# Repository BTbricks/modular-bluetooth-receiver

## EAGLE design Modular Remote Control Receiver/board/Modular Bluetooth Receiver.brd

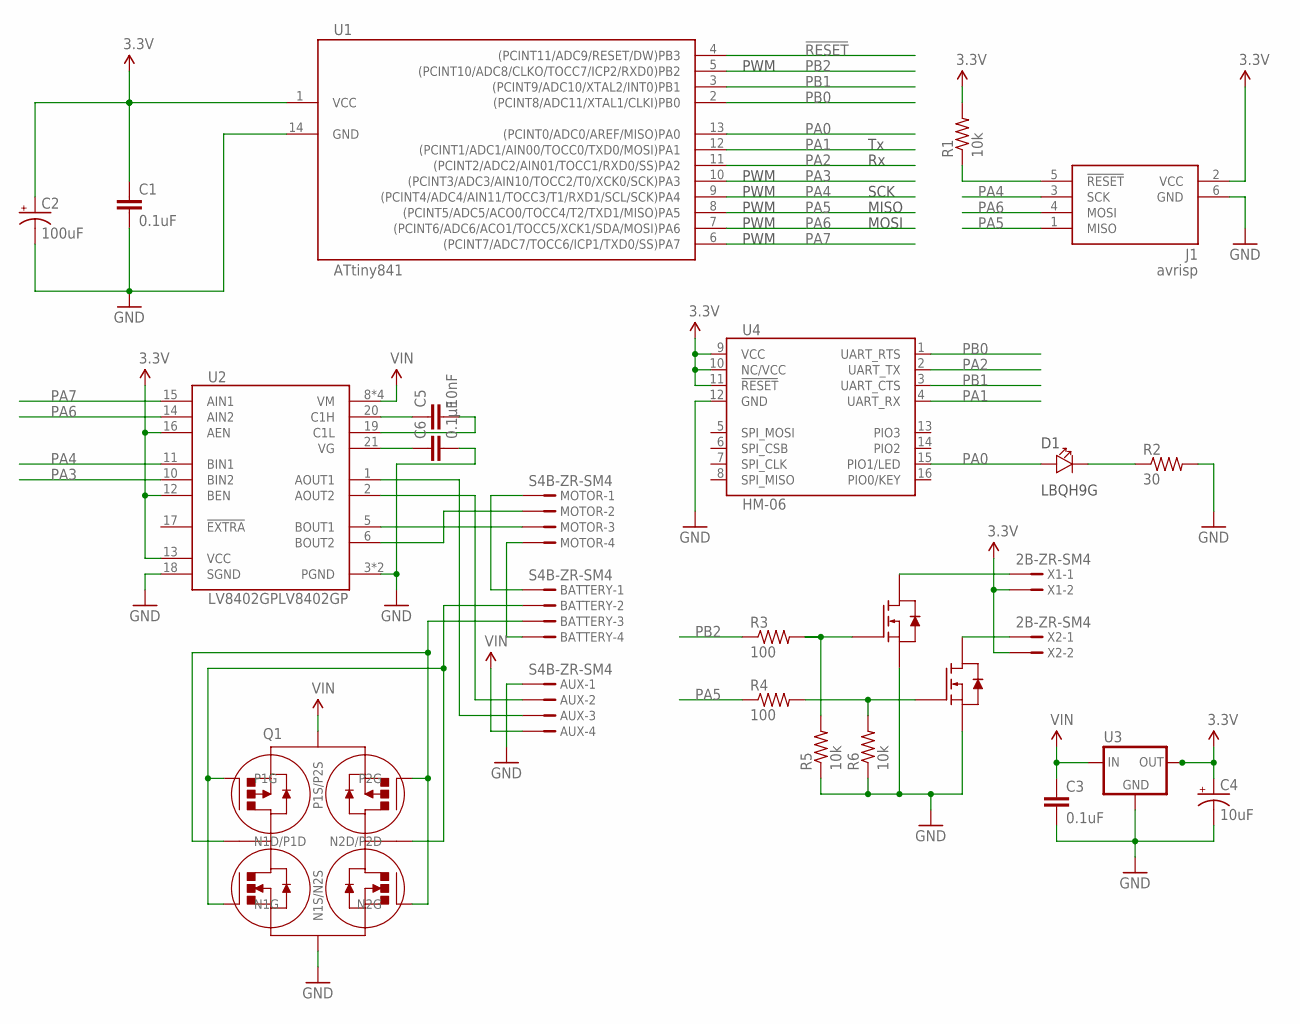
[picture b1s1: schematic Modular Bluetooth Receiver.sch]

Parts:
AUX: S4B-ZR-SM4
BATTERY: S4B-ZR-SM4
C1: 0.1uF; 0402; PARTNO 0603YC104KAT2A
C2: 100uF; 1206; PARTNO MCTT21X106M6R3CT
C3: 0.1uF; 0402
C4: 10uF; 1206
C5: 10nF; 0402
C6: 0.1µF; 0402
D1: LBQH9G; 0402_POL
J1: avrisp; CON6P2R
MOTOR: S4B-ZR-SM4
Q1: DMHC3025LSD-13; SO8
Q2: DMN32D2LV; SOT-563
R1, R5, R6: 10k; 0402; PARTNO ERJ-3GEYJ103V
R2: 30; 0402
R3, R4: 100; 0402
U1: ATtiny841; 14SOICN
U2: LV8402GPLV8402GP; VCT24
U3: RT9164A; SOT223
U4: HM-06; HM-05/06/07
X1, X2: 2B-ZR-SM4; S2B-ZR-SM4

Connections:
3.3V: C1.1, C2.1 (+), C4.1 (+), J1.2 (VCC), R1.2, U1.1 (VCC), U2.12 (BEN), U2.13 (VCC), U2.16 (AEN), U3.2 (OUT), U3.4 (OUT), U4.9 (VCC), U4.10 (NC/VCC), U4.11 (!RESET), X1.2, X2.2
!RESET: J1.5 (!RESET), R1.1, U1.4 ((PCINT11/ADC9/RESET/DW)PB3)
GND: AUX.1, C1.2, C2.2 (-), C3.2, C4.2 (-), C6.2, J1.6 (GND), Q1.P$3 (N1S/N2S), Q2.P$1 (SOURCE), Q2.P$4 (SOURCE), R2.2, R5.1, R6.1, U1.14 (GND), U2.3 (PGND), U2.4 (PGND), U2.18 (SGND), U3.1 (GND), U4.12 (GND)
unnamed: BATTERY.1, MOTOR.1
unnamed: BATTERY.4, MOTOR.4
unnamed: MOTOR.3, U2.5 (BOUT1)
unnamed: Q2.P$6 (DRAIN), X1.1
unnamed: AUX.3, U2.1 (AOUT1)
unnamed: AUX.2, U2.2 (AOUT2)
unnamed: BATTERY.2, Q1.P$1 (N1G), Q1.P$6 (N2D/P2D), Q1.P$8 (P1G)
unnamed: BATTERY.3, Q1.P$2 (N1D/P1D), Q1.P$4 (N2G), Q1.P$5 (P2G)
unnamed: C5.2, U2.19 (C1L)
unnamed: C6.1, U2.21 (VG)
unnamed: Q2.P$3 (DRAIN), X2.1
unnamed: D1.P$1, R2.1
unnamed: Q2.P$2 (GATE), R3.2, R5.2
unnamed: Q2.P$5 (GATE), R4.2, R6.2
unnamed: C5.1, U2.20 (C1H)
unnamed: MOTOR.2, U2.6 (BOUT2)
PA0: D1.P$2, U1.13 ((PCINT0/ADC0/AREF/MISO)PA0), U4.15 (PIO1/LED)
PA1: U1.12 ((PCINT1/ADC1/AIN00/TOCC0/TXD0/MOSI)PA1), U4.4 (UART_RX)
PA2: U1.11 ((PCINT2/ADC2/AIN01/TOCC1/RXD0/SS)PA2), U4.2 (UART_TX)
PA3: U1.10 ((PCINT3/ADC3/AIN10/TOCC2/T0/XCK0/SCK)PA3), U2.10 (BIN2)
PA4: J1.3 (SCK), U1.9 ((PCINT4/ADC4/AIN11/TOCC3/T1/RXD1/SCL/SC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), U2.11 (BIN1)
PA5: J1.1 (MISO), R4.1, U1.8 ((PCINT5/ADC5/ACO0/TOCC4/T2/TXD1/MISO)PA5)
PA6: J1.4 (MOSI), U1.7 ((PCINT6/ADC6/ACO1/TOCC5/XCK1/SDA/MOSI)P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), U2.14 (AIN2)
PA7: U1.6 ((PCINT7/ADC7/TOCC6/ICP1/TXD0/SS)PA7), U2.15 (AIN1)
PB0: U1.2 ((PCINT8/ADC11/XTAL1/CLKI)PB0), U4.1 (UART_RTS)
PB1: U1.3 ((PCINT9/ADC10/XTAL2/INT0)PB1), U4.3 (UART_CTS)
PB2: R3.1, U1.5 ((PCINT10/ADC8/CLKO/TOCC7/ICP2/RXD0)PB2)
VIN: AUX.4, C3.1, Q1.P$7 (P1S/P2S), U2.8 (VM), U2.9 (VM), U2.22 (VM), U2.23 (VM), U3.3 (IN)

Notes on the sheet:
MOSI
MISO
SCK
PWM

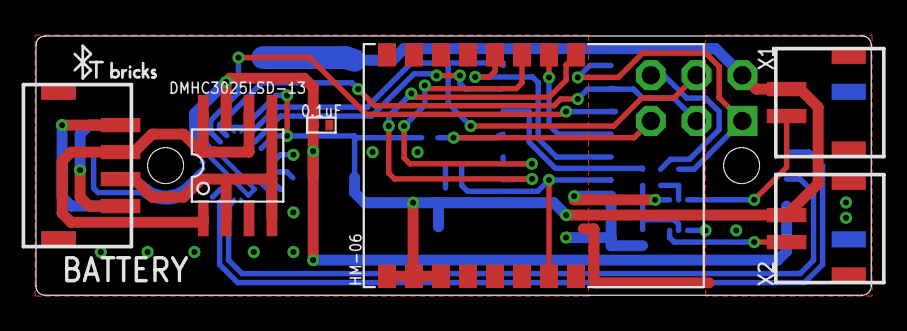
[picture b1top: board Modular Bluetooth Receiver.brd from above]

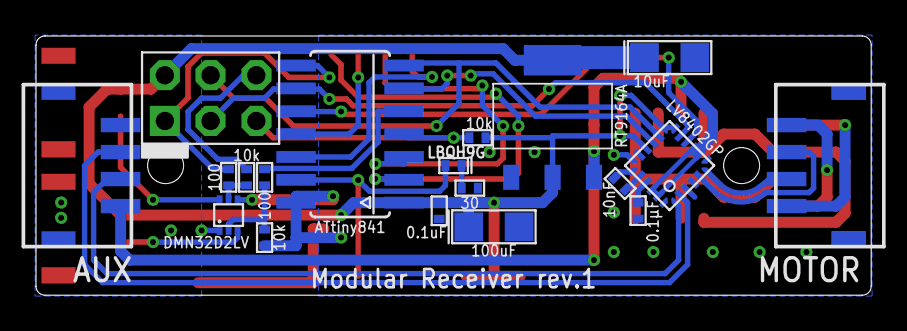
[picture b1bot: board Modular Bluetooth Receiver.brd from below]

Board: 2 copper layers, 46.4 x 14.4 mm, 25 parts (19 on the bottom side), 31 nets.

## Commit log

2016-01-10 Add directional lighting

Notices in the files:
parts and their libraries:
SparkFun-Aesthetics: Licensing: CC v3.0 Share-Alike You are welcome to use this library for commercial purposes.
